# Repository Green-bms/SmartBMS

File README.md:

# SmartBMS
Open source Smart Battery Management System

Youtube presentation:
https://youtu.be/0XNe25lMs6U?si=eK-90N3kao_sy4zy

Official page:
https://hackaday.io/project/181453-green-bms

## Description
Smart BMS is an Open Source Battery Management System for Lithium Cells (Lifepo4, Li-ion, NCM, etc.) Battery Pack.

The main functions of BMS are:
- To protect cells against overvoltage
- To protect cells against undervoltage
- To balance the cells 

Smart BMS consists of four main components:
1. Cell Module (https://hackaday.io/project/181453-green-bms/log/198376-green-bms-cell-module)
2. Control Unit (https://hackaday.io/project/181453-green-bms/log/198414-green-bms-control-unit)
3. Limiter (https://hackaday.io/project/181453-green-bms/log/198378-green-bms-limiter)
4. Android App (https://hackaday.io/project/181453-green-bms/log/198377-green-bms-android-app)

The voltage and the temperature values of each cell are acquired by the relevant Cell Module (based on Attiny microcontroller) and sent to Control Unit (based on Arduino Mega microcontroller) through a serial I2C line.

Control Unit starts or stop charging (by output relay) through Limiter, that includes a power relay for opening or closing the charging circuit.

Control Unit can also start or stop discharging by output relay.

When during charging a cell reaches the “Balance voltage value parameter”, the Cell Module connects the balance resistors in order to perform the cell bleeding.

When just one cell of the pack is balancing, Control Unit activates the current limit function inside the Limiter (the charging current is limited to 1A).

Control Unit can be connected with a Smartphone (or a Tablet) by Bluetooth.

By “Green BMS” Android app (available on Play Store) it is possible to check the Battery Pack status (total voltage, current load, state of charge…) , to check the actual voltage and temperature values of each cell and to perform several settings.

## Android App free download
The Green BMS Android app is available here: 
[Green-BMS App](https://play.google.com/store/apps/details?id=appinventor.ai_sergio_ghirardelli75.Green_bms_0_0&pcampaignid=pcampaignidMKT-Other-global-all-co-prtnr-py-PartBadge-Mar2515-1)

## Tutorials

Step by step instructions for make Green BMS are available here:
https://hackaday.io/project/181453/instructions

## Youtube channel

https://www.youtube.com/channel/UCdJnQnmzJSQNOAGbZR5iExA

Subscribe please... :smile:

## Open source Development applications

The project was created using the following Open source applications:
- **KiCad** : to design cell module and Interface board
- **QElectroTech** : to design Limiter
- **LibreCad 2D** : to desingn Control Unit Box
- **Arduino IDE** : to design the code of Cell Module(Attiny) and Control Unit(Arduino Mega)
- **Mit App Inventor** : to design the Android Application

## Warning

Lithium and other batteries are dangerous and must be treated with care.

Lithium and other batteries are potentially hazardous and can present a serious fire hazard if damaged, defective or improperly used.

Green BMS is a "do it yourself" project, with no warranties whatsoever.

Green BMS assumes no responsibility for any errors or inaccuracies that may appear in any documentation or file or any software that may be provided.

The use of this project is done entirely at your own risk and responsibility.

The use of this project may not be compliant with local laws or regulations.

## Open Source Hardware Certification

Green BMS has been certified as open source hardware by the Open Source Hardware Association, with the UID: IT000007.

Certificate link: (https://certification.oshwa.org/it000007.html)

## License

This work is licensed under a **Creative Commons Attribution-ShareAlike 4.0 International License**.
https://creativecommons.org/licenses/by-sa/4.0/

### You are free to:

**Share** — copy and redistribute the material in any medium or format

**Adapt**  — remix, transform, and build upon the material
for any purpose, even commercially.
This license is acceptable for Free Cultural Works.
The licensor cannot revoke these freedoms as long as you follow the license terms.

### Under the following terms:

**Attribution** — You must give appropriate credit, provide a link to the license, and indicate if changes were made. You may do so in any reasonable manner, but not in any way that suggests the licensor endorses you or your use.

**ShareAlike** — If you remix, transform, or build upon the material, you must distribute your contributions under the same license as the original.

**No additional restrictions** — You may not apply legal terms or technological measures that legally restrict others from doing anything the license permits.

### Notices:
You do not have to comply with the license for elements of the material in the public domain or where your use is permitted by an applicable exception or limitation.
No warranties are given. The license may not give you all of the permissions necessary for your intended use. For example, other rights such as publicity, privacy, or moral rights may limit how you use the material.

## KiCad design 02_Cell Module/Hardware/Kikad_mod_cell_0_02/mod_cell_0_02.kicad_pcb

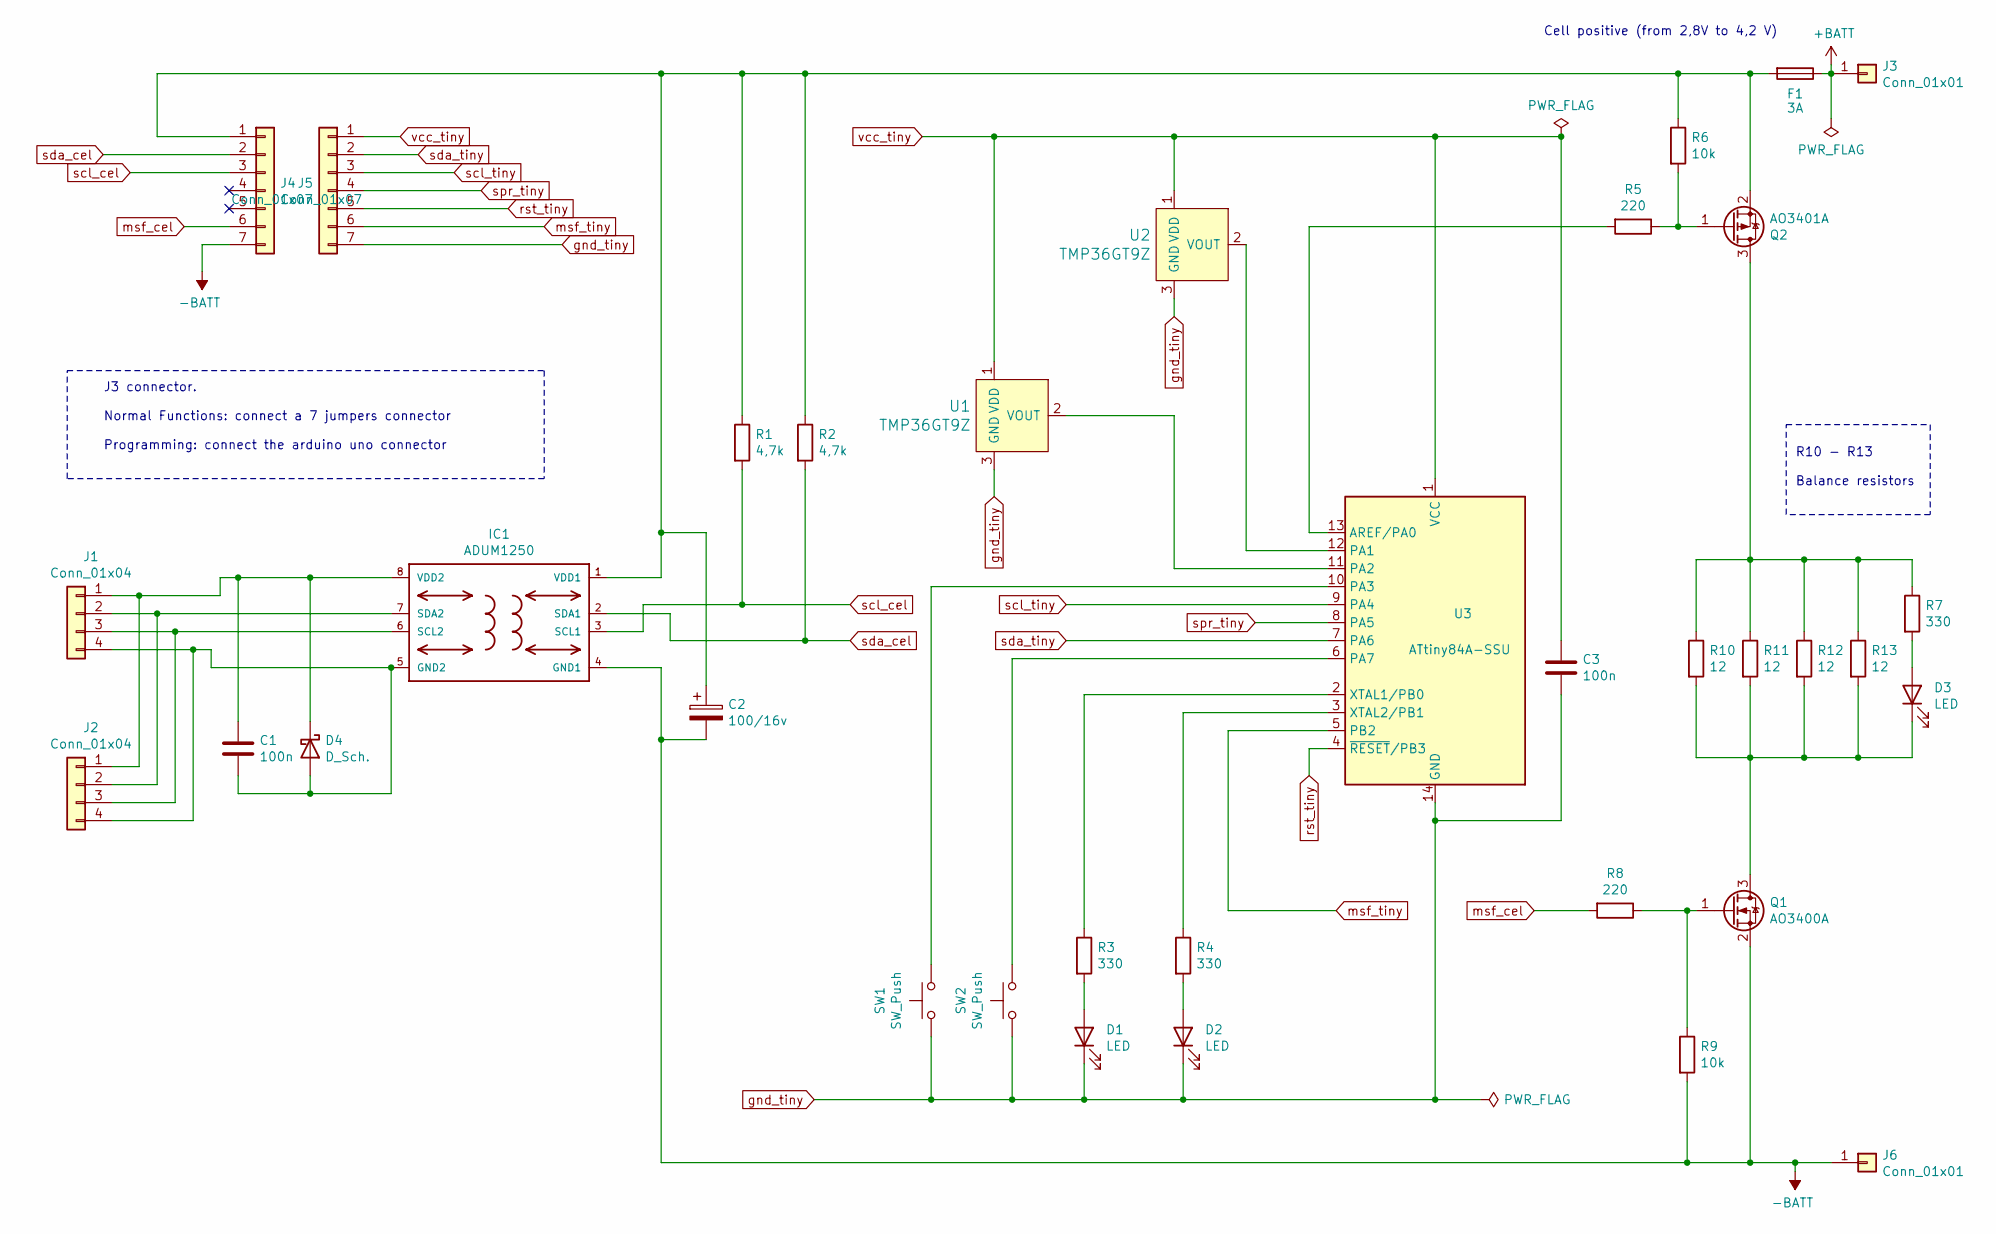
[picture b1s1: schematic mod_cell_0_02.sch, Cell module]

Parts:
C1, C3: 100n; C_1206_3216Metric
C2: 100/16v; CP_Elec_6.3x5.8
D1, D2, D3: LED; LED_1206_3216Metric
D4: D_Sch.; D_SMA
F1: 3A; Fuse_1206_3216Metric
IC1: ADUM1250; SOIC-8_3.9x4.9mm_P1.27mm
J1, J2: Conn_01x04; JST_PH_B4B-PH-K_1x04_P2.00mm_Vertical
J3: Conn_01x01; SolderWire-battery_cell_pole_2
J4, J5: Conn_01x07; JST_PH_B7B-PH-K_1x07_P2.00mm_Vertical
J6: Conn_01x01; SolderWire-battery_cell_for_wire_2
Q1: AO3400A; SOT-23
Q2: AO3401A; SOT-23
R1, R2: 4,7k; R_1206_3216Metric
R3, R4, R7: 330; R_1206_3216Metric
R5, R8: 220; R_1206_3216Metric
R6, R9: 10k; R_1206_3216Metric
R10, R11, R12, R13: 12; R_Axial_DIN0922_L20.0mm_D9.0mm_P25.40mm_Horizontal
SW1, SW2: SW_Push; SW_Push_SPST_NO_Alps_SKRK
U1, U2: TMP36GT9Z; TO-92-3; MPN TMP36GT9Z; Digi-Key_PN TMP36GT9Z-ND
U3: ATtiny84A-SSU; SOIC-14_3.9x8.7mm_P1.27mm

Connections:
+BATT: F1.1, J3.1
-BATT: C2.2, IC1.4 (GND1), J4.7, J6.1, Q1.2 (S), R9.2
unnamed: C1.1, D4.1 (K), IC1.8 (VDD2), J1.1, J2.1
unnamed: C1.2, D4.2 (A), IC1.5 (GND2), J1.4, J2.4
unnamed: C2.1, F1.2, IC1.1 (VDD1), J4.1, Q2.2 (S), R1.1, R2.1, R6.1
unnamed: D1.2 (A), R3.2
unnamed: D2.2 (A), R4.2
unnamed: D3.1 (K), Q1.3 (D), R10.2, R11.2, R12.2, R13.2
unnamed: D3.2 (A), R7.2
unnamed: IC1.6 (SCL2), J1.3, J2.3
unnamed: IC1.7 (SDA2), J1.2, J2.2
unnamed: Q1.1 (G), R8.1, R9.1
unnamed: Q2.1 (G), R5.1, R6.2
unnamed: Q2.3 (D), R7.1, R10.1, R11.1, R12.1, R13.1
unnamed: R3.1, U3.2 (XTAL1/PB0)
unnamed: R4.1, U3.3 (XTAL2/PB1)
unnamed: R5.2, U3.13 (AREF/PA0)
unnamed: SW1.2, U3.10 (PA3)
unnamed: SW2.2, U3.6 (PA7)
unnamed: U1.2 (VOUT), U3.11 (PA2)
unnamed: U2.2 (VOUT), U3.12 (PA1)
gnd_tiny: C3.2, D1.1 (K), D2.1 (K), J5.7, SW1.1, SW2.1, U1.3 (GND), U2.3 (GND), U3.14 (GND)
msf_cel: J4.6, R8.2
msf_tiny: J5.6, U3.5 (PB2)
rst_tiny: J5.5, U3.4 (~RESET~/PB3)
scl_cel: IC1.3 (SCL1), J4.3, R1.2
scl_tiny: J5.3, U3.9 (PA4)
sda_cel: IC1.2 (SDA1), J4.2, R2.2
sda_tiny: J5.2, U3.7 (PA6)
spr_tiny: J5.4, U3.8 (PA5)
vcc_tiny: C3.1, J5.1, U1.1 (VDD), U2.1 (VDD), U3.1 (VCC)

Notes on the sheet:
Cell positive (from 2,8V to 4,2 V)
J3 connector. Normal Functions: connect a 7 jumpers connector Programming: connect the arduino uno connector
R10 - R13 Balance resistors

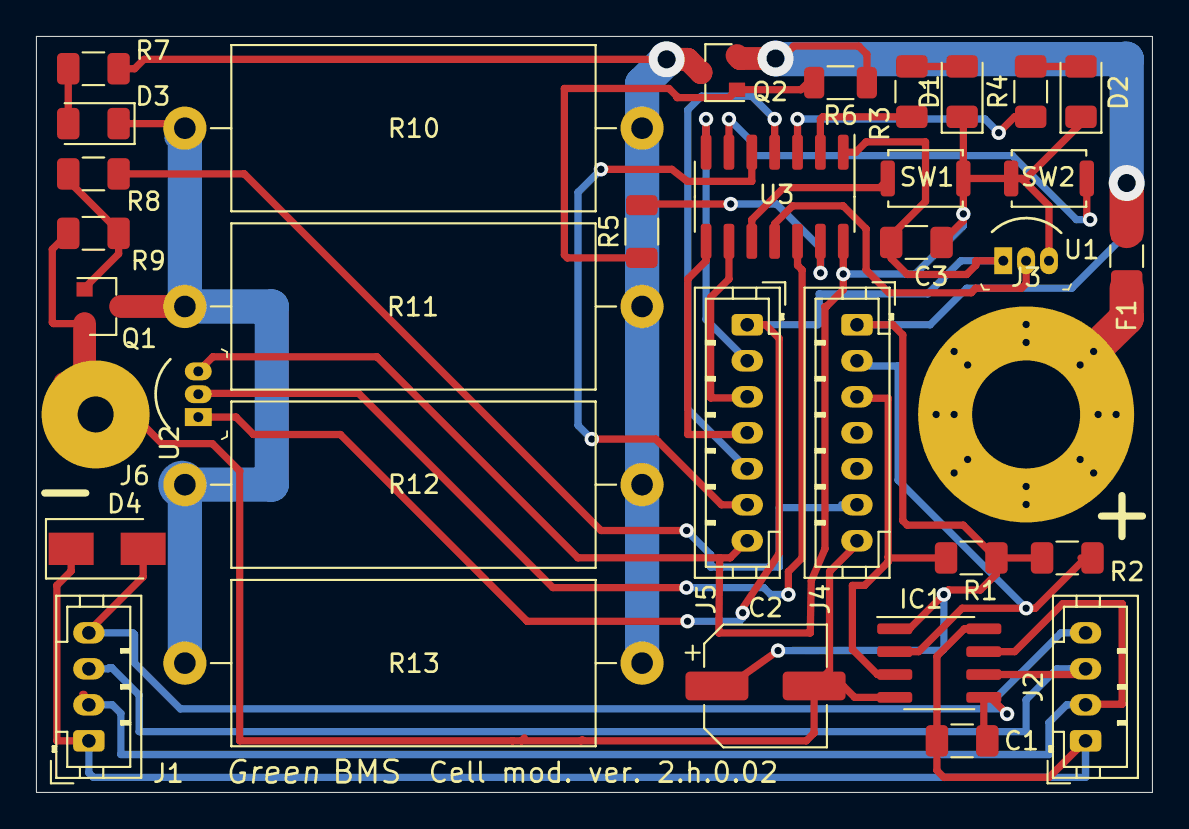
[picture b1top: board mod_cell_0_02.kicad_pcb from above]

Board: 2 copper layers, 62.0 x 42.0 mm, 35 parts (0 on the bottom side), 31 nets.

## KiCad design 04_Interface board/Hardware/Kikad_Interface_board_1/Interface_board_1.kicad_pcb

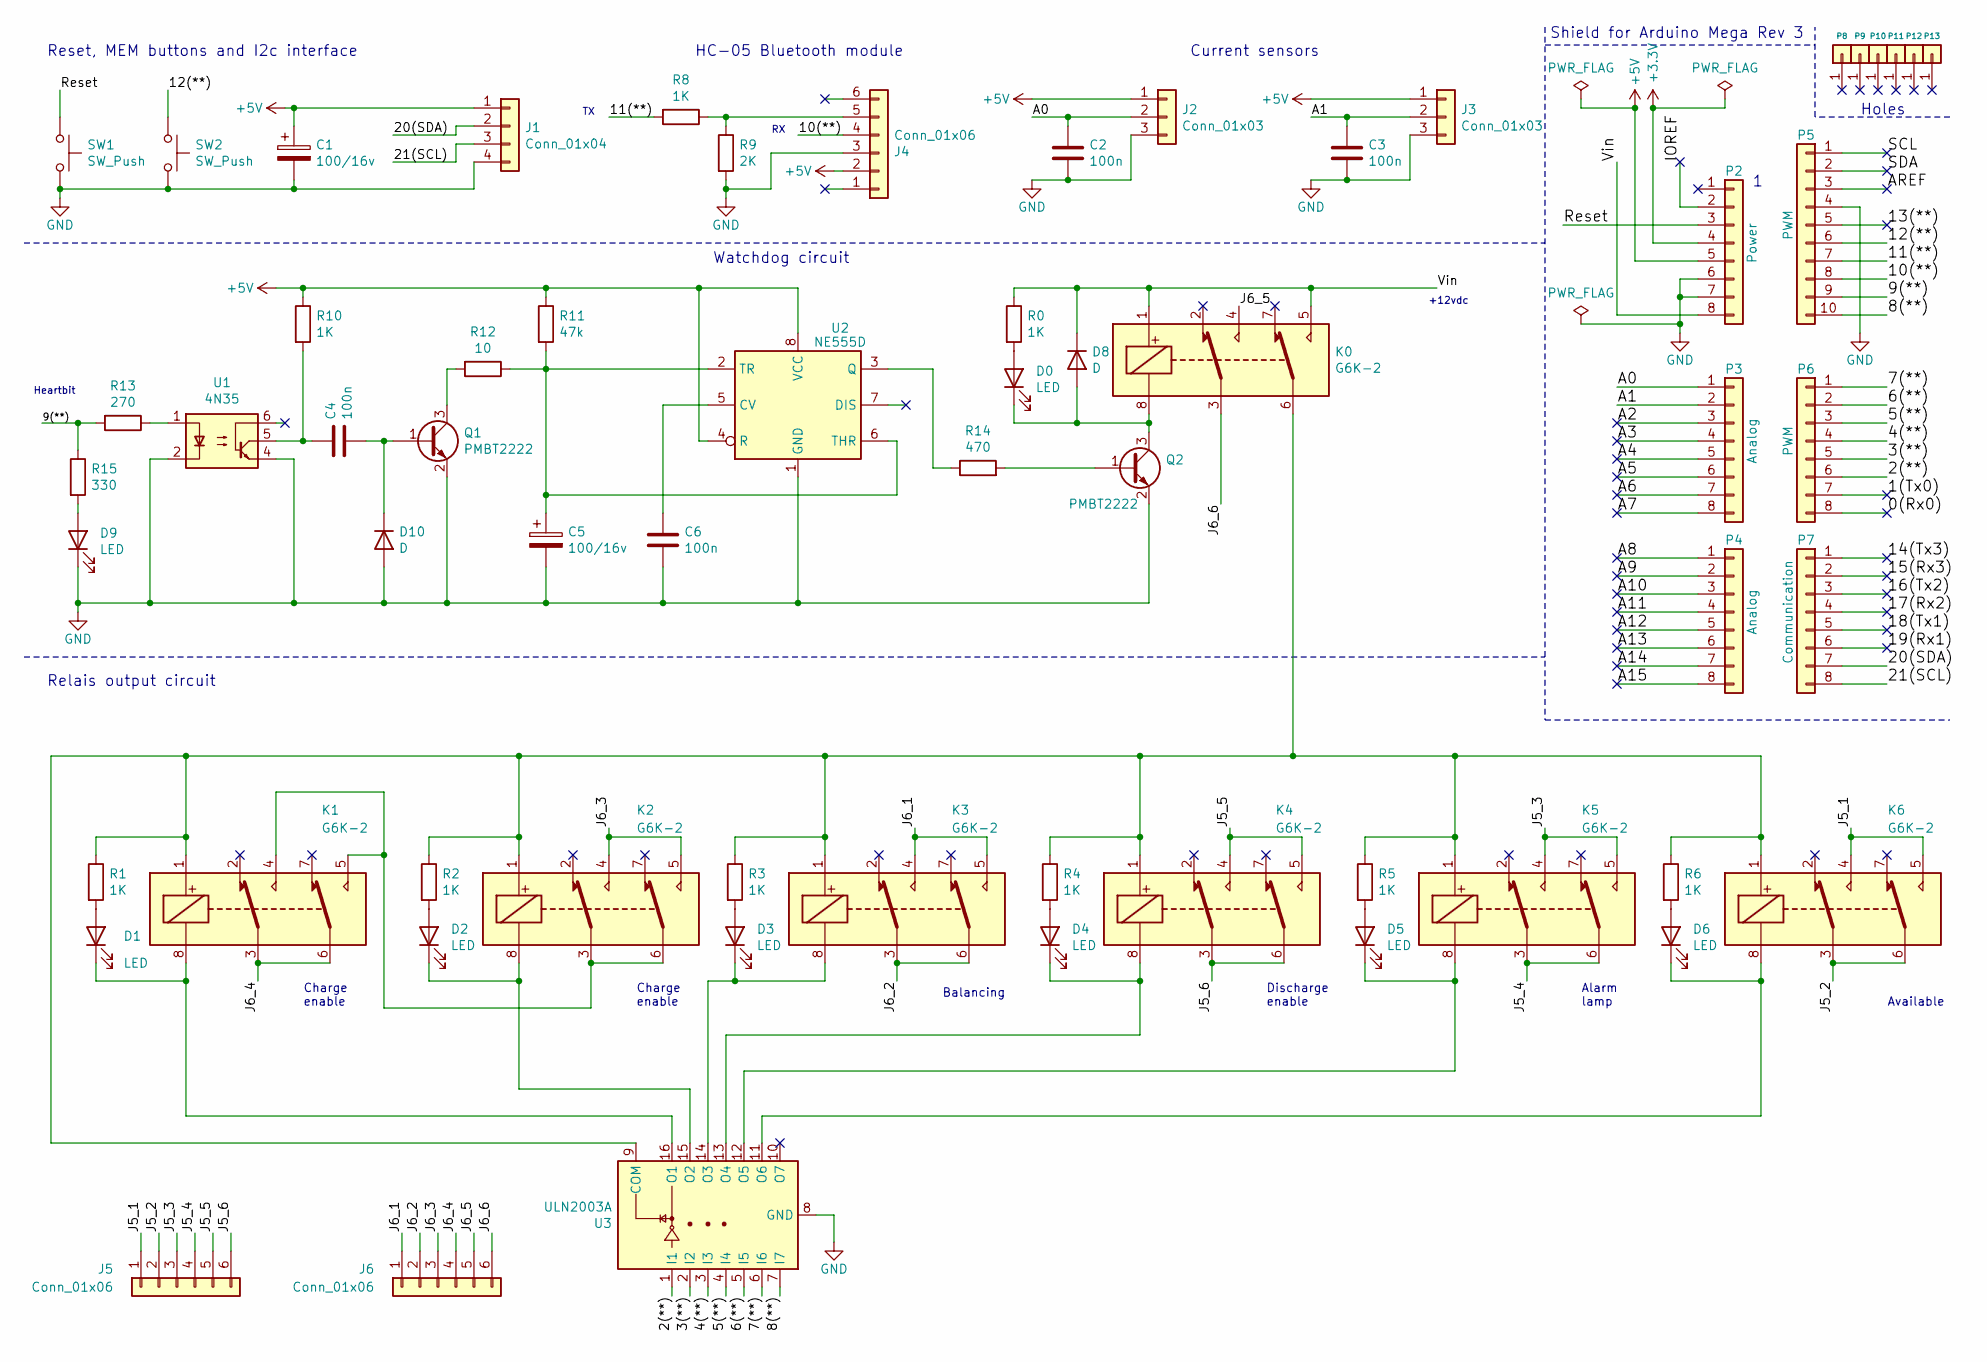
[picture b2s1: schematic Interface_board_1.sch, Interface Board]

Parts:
C1, C5: 100/16v; CP_Elec_6.3x5.8
C2, C3, C4, C6: 100n; C_1206_3216Metric
D0, D1, D2, D3, D4, D5, D6, D9: LED; LED_1206_3216Metric
D8, D10: D; D_1206_3216Metric
J1: Conn_01x04; JST_PH_S4B-PH-K_1x04_P2.00mm_Horizontal
J2, J3: Conn_01x03; JST_PH_S3B-PH-K_1x03_P2.00mm_Horizontal
J4: Conn_01x06; PinSocket_1x06_P2.54mm_Horizontal
J5, J6: Conn_01x06; PhoenixContact_MC_1,5_6-G-3.5_1x06_P3.50mm_Horizontal
K0, K1, K2, K3, K4, K5, K6: G6K-2; Relay_DPDT_Omron_G6K-2F-Y
P2: Power; Socket_Strip_Arduino_1x08
P3, P4: Analog; Socket_Strip_Arduino_1x08
P5: PWM; Socket_Strip_Arduino_1x10
P6: PWM; Socket_Strip_Arduino_1x08
P7: Communication; Socket_Strip_Arduino_1x08
P8, P9, P10, P11, P12, P13: CONN_01X01; Arduino_1pin
Q1, Q2: PMBT2222; SOT-23
R0, R1, R2, R3, R4, R5, R6, R8, R10: 1K; R_1206_3216Metric
R9: 2K; R_1206_3216Metric
R11: 47k; R_1206_3216Metric
R12: 10; R_1206_3216Metric
R13: 270; R_1206_3216Metric
R14: 470; R_1206_3216Metric
R15: 330; R_1206_3216Metric
SW1, SW2: SW_Push; SW_Push_SPST_NO_Alps_SKRK
U1: 4N35; DIP-6_W7.62mm
U2: NE555D; SOIC-8_3.9x4.9mm_P1.27mm
U3: ULN2003A; SOIC-16_3.9x9.9mm_P1.27mm

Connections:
+3V3: P2.4
+5V: C1.1, J1.1, J2.1, J3.1, J4.2, P2.5, R10.1, R11.1, U2.4 (R), U2.8 (VCC)
/0(Rx0): P6.8
/1(Tx0): P6.7
/2(**): P6.6, U3.1 (I1)
/3(**): P6.5, U3.2 (I2)
/4(**): P6.4, U3.3 (I3)
/5(**): P6.3, U3.4 (I4)
/6(**): P6.2, U3.5 (I5)
/7(**): P6.1, U3.6 (I6)
/8(**): P5.10, U3.7 (I7)
/9(**): P5.9, R13.2, R15.1
/10(**): J4.4, P5.8
/11(**): P5.7, R8.2
/12(**): P5.6, SW2.1
/13(**): P5.5
/14(Tx3): P7.1
/15(Rx3): P7.2
/16(Tx2): P7.3
/17(Rx2): P7.4
/18(Tx1): P7.5
/19(Rx1): P7.6
/20(SDA): J1.2, P7.7
/21(SCL): J1.3, P7.8
/A0: C2.1, J2.2, P3.1
/A1: C3.1, J3.2, P3.2
/A2: P3.3
/A3: P3.4
/A4: P3.5
/A5: P3.6
/A6: P3.7
/A7: P3.8
/A8: P4.1
/A9: P4.2
/A10: P4.3
/A11: P4.4
/A12: P4.5
/A13: P4.6
/A14: P4.7
/A15: P4.8
/AREF: P5.3
/IOREF: P2.2
/J5_1: J5.1, K6.4, K6.5
/J5_2: J5.2, K6.3, K6.6
/J5_3: J5.3, K5.4, K5.5
/J5_4: J5.4, K5.3, K5.6
/J5_5: J5.5, K4.4, K4.5
/J5_6: J5.6, K4.3, K4.6
/J6_1: J6.1, K3.4, K3.5
/J6_2: J6.2, K3.3, K3.6
/J6_3: J6.3, K2.4, K2.5
/J6_4: J6.4, K1.3, K1.6
/J6_5: J6.5, K0.4
/J6_6: J6.6, K0.3
/Reset: P2.3, SW1.1
/SCL: P5.1
/SDA: P5.2
/Vin: D8.1 (K), K0.1, K0.5, P2.8, R0.1
GND: C1.2, C2.2, C3.2, C5.2, C6.2, D9.1 (K), D10.2 (A), J1.4, J2.3, J3.3, J4.3, P2.6, P2.7, P5.4, Q1.2 (E), Q2.2 (E), R9.2, SW1.2, SW2.2, U1.2, U1.4, U2.1 (GND), U3.8 (GND)
unnamed: C4.1, R10.2, U1.5
unnamed: C4.2, D10.1 (K), Q1.1 (B)
unnamed: C5.1, R11.2, R12.1, U2.2 (TR), U2.6 (THR)
unnamed: C6.1, U2.5 (CV)
unnamed: D0.1 (K), D8.2 (A), K0.8, Q2.3 (C)
unnamed: D0.2 (A), R0.2
unnamed: D1.1 (K), K1.8, U3.16 (O1)
unnamed: D1.2 (A), R1.2
unnamed: D2.1 (K), K2.8, U3.15 (O2)
unnamed: D2.2 (A), R2.2
unnamed: D3.1 (K), K3.8, U3.14 (O3)
unnamed: D3.2 (A), R3.2
unnamed: D4.1 (K), K4.8, U3.13 (O4)
unnamed: D4.2 (A), R4.2
unnamed: D5.1 (K), K5.8, U3.12 (O5)
unnamed: D5.2 (A), R5.2
unnamed: D6.1 (K), K6.8, U3.11 (O6)
unnamed: D6.2 (A), R6.2
unnamed: D9.2 (A), R15.2
unnamed: J4.5, R8.1, R9.1
unnamed: K0.6, K1.1, K2.1, K3.1, K4.1, K5.1, K6.1, R1.1, R2.1, R3.1, R4.1, R5.1, R6.1, U3.9 (COM)
unnamed: K1.4, K1.5, K2.3, K2.6
unnamed: Q1.3 (C), R12.2
unnamed: Q2.1 (B), R14.2
unnamed: R13.1, U1.1
unnamed: R14.1, U2.3 (Q)

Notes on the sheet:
Holes
Shield for Arduino Mega Rev 3
Reset, MEM buttons and I2c interface
Current sensors
HC-05 Bluetooth module
Heartbit
Watchdog circuit
+12vdc
Charge enable
Discharge enable
Balancing
Alarm lamp
Available
Relais output circuit

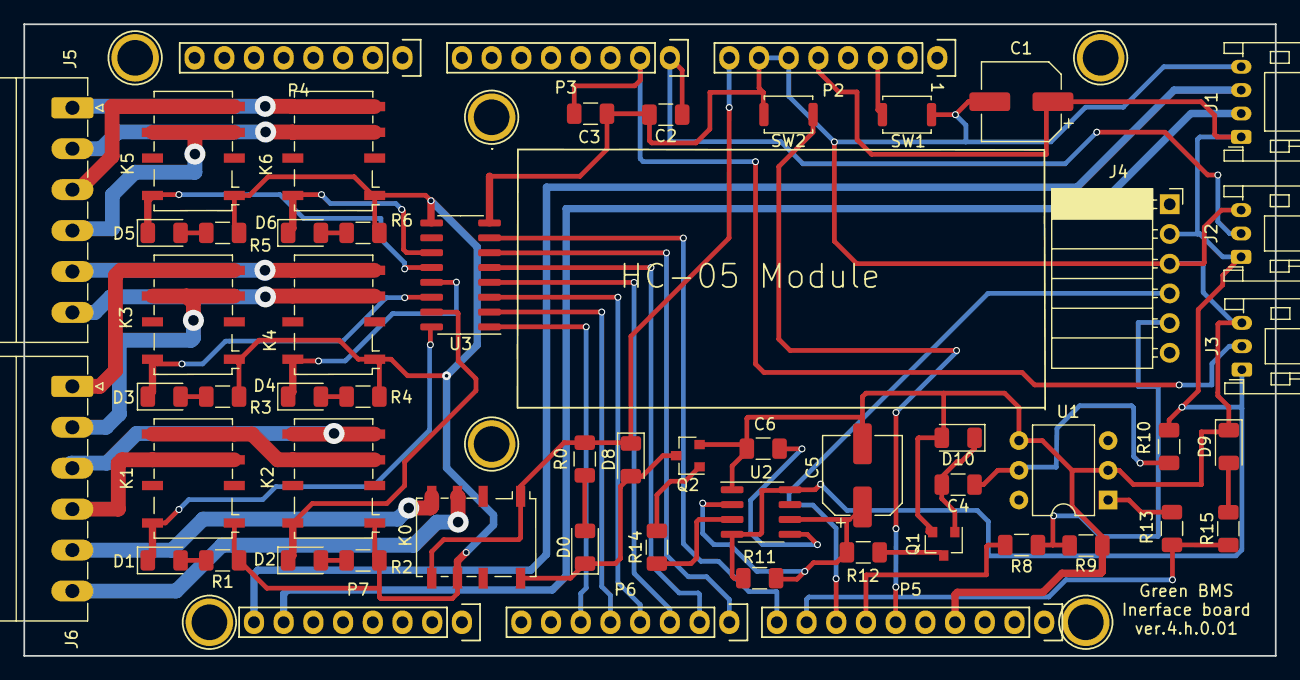
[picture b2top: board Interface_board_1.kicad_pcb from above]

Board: 2 copper layers, 107.0 x 54.0 mm, 63 parts (0 on the bottom side), 57 nets.

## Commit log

2021-08-26 First release
2021-08-26 Create License
2021-08-28 added OSHWA, new video link and App link
2021-09-16 removed LTO batteries , added new tutorials
2021-10-03 Modified links
2021-10-05 modified tutorial link
2023-12-08 Update README.md
    added buy me a coffee button
